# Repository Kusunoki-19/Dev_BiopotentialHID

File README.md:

# Development of BiopotentailHID(Human Interface Device)

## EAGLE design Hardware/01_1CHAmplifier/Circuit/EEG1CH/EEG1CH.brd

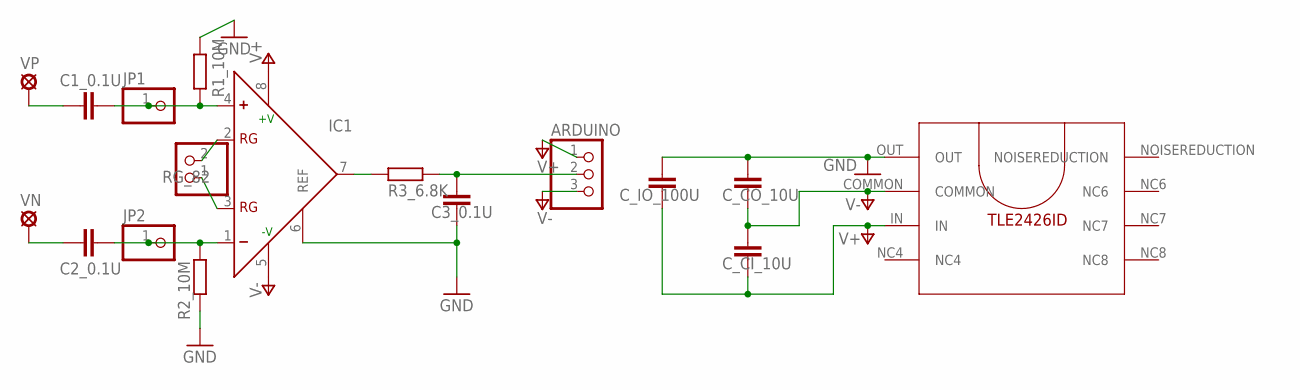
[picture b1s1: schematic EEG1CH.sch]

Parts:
ARDUINO: PINHD-1X3; 1X03
C1_0.1U, C2_0.1U, C3_0.1U: C2,5-3; C2.5-3
C_CI_10U: C2,5-3; C2.5-3
C_CO_10U: C2,5-3; C2.5-3
C_IO_100U: C2,5-3; C2.5-3
IC1: AD8227; SO8
JP1, JP2: PINHD-1X1; 1X01
R1_10M, R2_10M, R3_6.8K: R-EU_R2012; R2012
RG_82: PINHD-1X2; 1X02
U$1: TLE2426ID
VN: SE13
VP: SE13

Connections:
GND: C3_0.1U.2, C_CO_10U.1, C_IO_100U.1, IC1.6 (REF), R1_10M.2, R2_10M.1, U$1.OUT
unnamed: IC1.2 (RG), RG_82.2
unnamed: IC1.3 (RG), RG_82.1
OUT-C-R: IC1.7 (OUT), R3_6.8K.2
R-C-IN: C2_0.1U.2, IC1.1 (-), JP2.1, R2_10M.2
R-C-IN2: C1_0.1U.2, IC1.4 (+), JP1.1, R1_10M.1
R-VO: ARDUINO.2, C3_0.1U.1, R3_6.8K.1
V+: ARDUINO.1, C_CI_10U.2, C_IO_100U.2, IC1.8 (+V), U$1.IN
V-: ARDUINO.3, C_CI_10U.1, C_CO_10U.2, IC1.5 (-V), U$1.COMMON
VN-C: C2_0.1U.1, VN.MP
VP-C: C1_0.1U.1, VP.MP

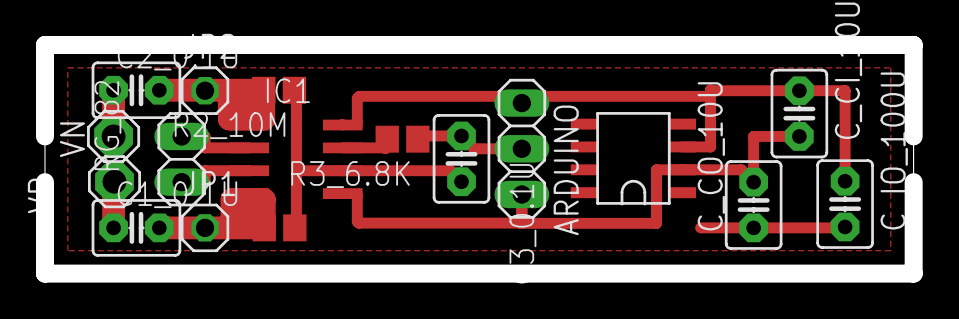
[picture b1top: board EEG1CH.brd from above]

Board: 2 copper layers, 48.3 x 12.7 mm, 17 parts (0 on the bottom side), 11 nets.

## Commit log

2021-10-10 UpdateReadme
2021-10-10 1CH増幅器と、作成途中のSerialMonitorアプリの追加
2021-10-14 Update issue templates
2021-10-14 Add project goal image to README.md and some text added
2021-10-14 add current goal image
2021-10-15 README一通り書き上げ
2021-10-15 誤字修正
2021-10-15 Update README
2021-10-20 Readme編集
2021-11-25 プロジェクトの利用方法とリポジトリ構造、参加方法の初版追加
2021-11-25 リポジトリ構造の修正
